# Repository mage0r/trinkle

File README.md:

Trinkle - The tiny breakout board for the ATTiny 84
=============

This project is a simple breakout board for the attiny84.

So, having bulk ordered to save a bit of cash, I have a lot of these attiny 84's.  They're a great, cheap little chip and sometimes you just need a few more pins than the 85 has.

This board has such features as: A Power LED, a blink LED attached to D8 and pin spacing to suit a protoboard.  It lacks features like anything else.

Version 2.0 now includes a USB port to upload sketches.  Software coming soon.

There are three sections, the circuit design for kicad, a few photos of the finished product and some working examples..

CREDITS
------------

This project was designed by John Spencer - john.spencer.9000@gmail.com - https://github.com/mage0r

Made at hackmelbourne.org!

SPECIAL THANKS
------------

To the HackMelbourne (CCHS, http://hackmelbourne.org) community of Melbourne, Australia.

To all other open-source developers whose countless hours supported every other aspect of this design.

DISTRIBUTION
------------
The specific terms of distribution of this project are governed by the
license referenced below. Please contact the copyright owner if you wish to modify the board for distribution. Please utilize this design for personal or research projects. Please acknowledge all contributors.

LICENSE
-------
Licensed under the TAPR Open Hardware License (www.tapr.org/OHL).
The "license" sub-folder also contains a copy of this license in plain text format.

Copyright John Spencer 2014
john.spencer.9000@gmail.com

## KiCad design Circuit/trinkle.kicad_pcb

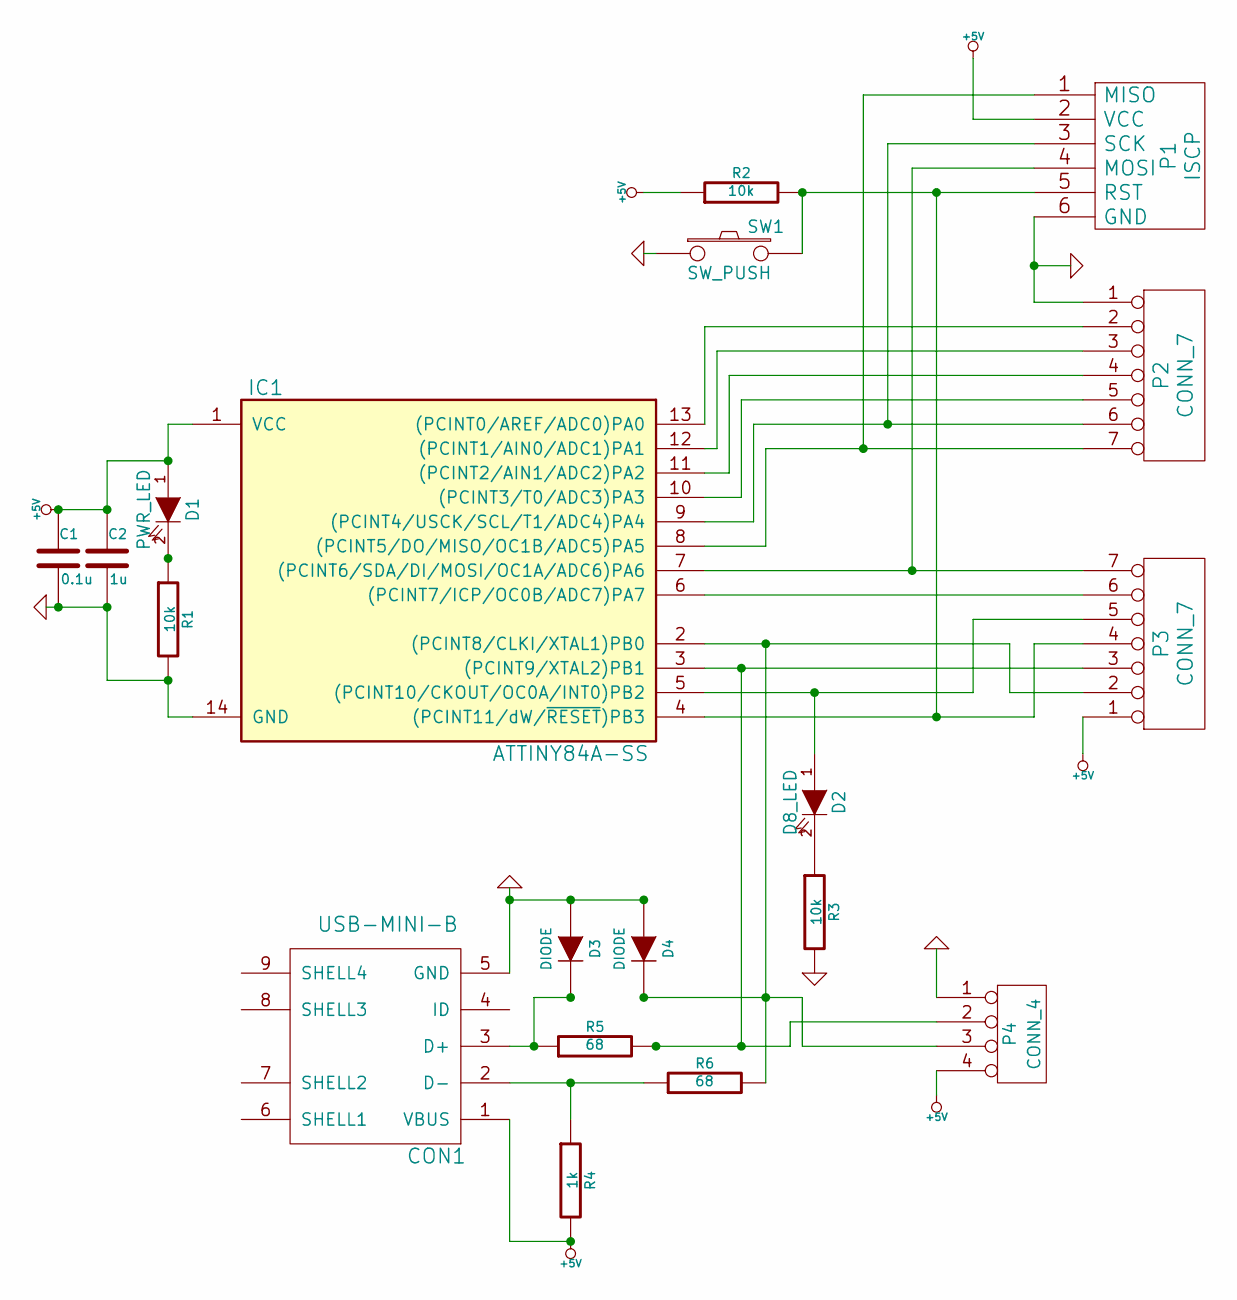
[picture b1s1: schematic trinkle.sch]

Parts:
C1: 0.1u
C2: 1u
CON1: USB-MINI-B
D1: PWR_LED
D2: D8_LED
D3, D4: DIODE
IC1: ATTINY84A-SS; SO14
P1: ISCP
P2, P3: CONN_7
P4: CONN_4
R1, R2, R3: 10k
R4: 1k
R5, R6: 68
SW1: SW_PUSH

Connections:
+5V: C1.1, C2.1, CON1.1 (VBUS), D1.1 (A), IC1.1 (VCC), P1.2 (VCC), P3.1, P4.4, R2.1, R4.2
GND: C1.2, C2.2, CON1.5 (GND), D3.1 (A), D4.1 (A), IC1.14 (GND), P1.6 (GND), P2.1, P4.1, R1.2, R3.2, SW1.1
unnamed: D2.2 (K), R3.1
unnamed: CON1.3 (D+), D3.2 (K), R5.1
unnamed: CON1.2 (D-), R4.1, R6.1
unnamed: D1.2 (K), R1.1
unnamed: IC1.11 ((PCINT2/AIN1/ADC2)PA2), P2.4
unnamed: D4.2 (K), IC1.2 ((PCINT8/CLKI/XTAL1)PB0), P3.2, P4.3, R6.2
unnamed: IC1.3 ((PCINT9/XTAL2)PB1), P3.3, P4.2, R5.2
unnamed: IC1.4 ((PCINT11/dW/~RESET~)PB3), P1.5 (RST), P3.4, R2.2, SW1.2
unnamed: D2.1 (A), IC1.5 ((PCINT10/CKOUT/OC0A/INT0)PB2), P3.5
unnamed: IC1.6 ((PCINT7/ICP/OC0B/ADC7)PA7), P3.6
unnamed: IC1.7 ((PCINT6/SDA/DI/MOSI/OC1A/ADC6)PA6), P1.4 (MOSI), P3.7
unnamed: IC1.8 ((PCINT5/DO/MISO/OC1B/ADC5)PA5), P1.1 (MISO), P2.7
unnamed: IC1.9 ((PCINT4/USCK/SCL/T1/ADC4)PA4), P1.3 (SCK), P2.6
unnamed: IC1.10 ((PCINT3/T0/ADC3)PA3), P2.5
unnamed: IC1.12 ((PCINT1/AIN0/ADC1)PA1), P2.3
unnamed: IC1.13 ((PCINT0/AREF/ADC0)PA0), P2.2

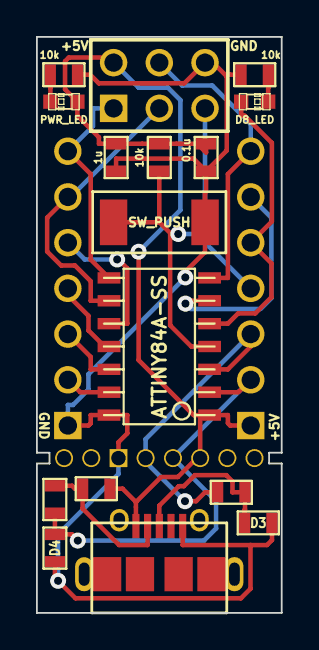
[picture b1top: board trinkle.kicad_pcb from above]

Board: 2 copper layers, 13.6 x 32.0 mm, 19 parts (0 on the bottom side), 18 nets.

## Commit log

2014-07-02 Initial commit
    Version 1.0 of the circuit
2014-07-02 Added photos and readme
2014-07-11 Added Arduino sketches
    Just examples with the right pin to use the on board LED.
2014-07-13 Added assembled photo
    Turns out, I don't have any 603 components or led's at the moment :)
2014-07-16 Added pdf of schematic
2014-07-21 Photos and readme update
2014-07-25 Added dependency link and updated photo.
2014-08-31 Added usb port
    Snap off capable usb port section
2014-09-22 Added new board photos and readme
2014-09-22 Whoops, wrong image.
2014-09-22 *sigh*
2014-09-22 damnit.
